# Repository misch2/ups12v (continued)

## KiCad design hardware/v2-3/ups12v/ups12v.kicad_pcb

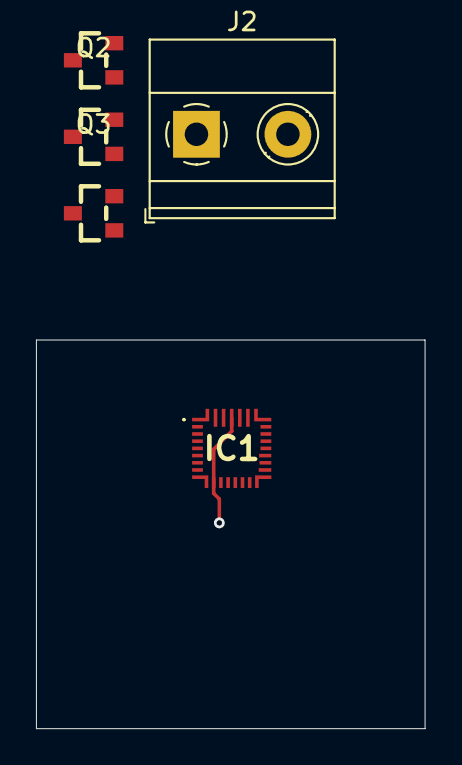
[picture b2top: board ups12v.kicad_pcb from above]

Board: 4 copper layers, 21.6 x 21.6 mm, 5 parts (0 on the bottom side), 10 nets.

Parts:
IC1: BQ25798RQMR
J2: BATTERY (BMS); TerminalBlock_Phoenix_MKDS-1,5-2-5.08_1x02_P5.08mm_Horizont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
Q1, Q2, Q3: SI2312CDS-T1-GE3; SOT-23_L2.9-W1.3-P1.90-LS2.4-BR

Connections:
BAT: IC1.22 (BAT_1), IC1.23 (BAT_2), Q3.2 (S)
GND: IC1.10 (ACDRV2), IC1.13 (~CE), IC1.27 (GND), J2.2
unnamed: Q1.2 (S), Q2.2 (S)
unnamed: Q1.1 (G), Q2.1 (G)
unnamed: J2.1, Q3.3 (D)
SDRV: IC1.24 (SDRV_1), IC1.33 (SDRV_2), Q3.1 (G)
STAT: IC1.1 (STAT_1), IC1.30 (STAT_2)
TS: IC1.16 (TS_1), IC1.32 (TS_2)
VBUS: IC1.2 (VBUS_1), IC1.3 (VBUS_2), IC1.8 (VAC2), Q2.3 (D)
VIN1: IC1.9 (VAC1_1), IC1.31 (VAC1_2), Q1.3 (D)

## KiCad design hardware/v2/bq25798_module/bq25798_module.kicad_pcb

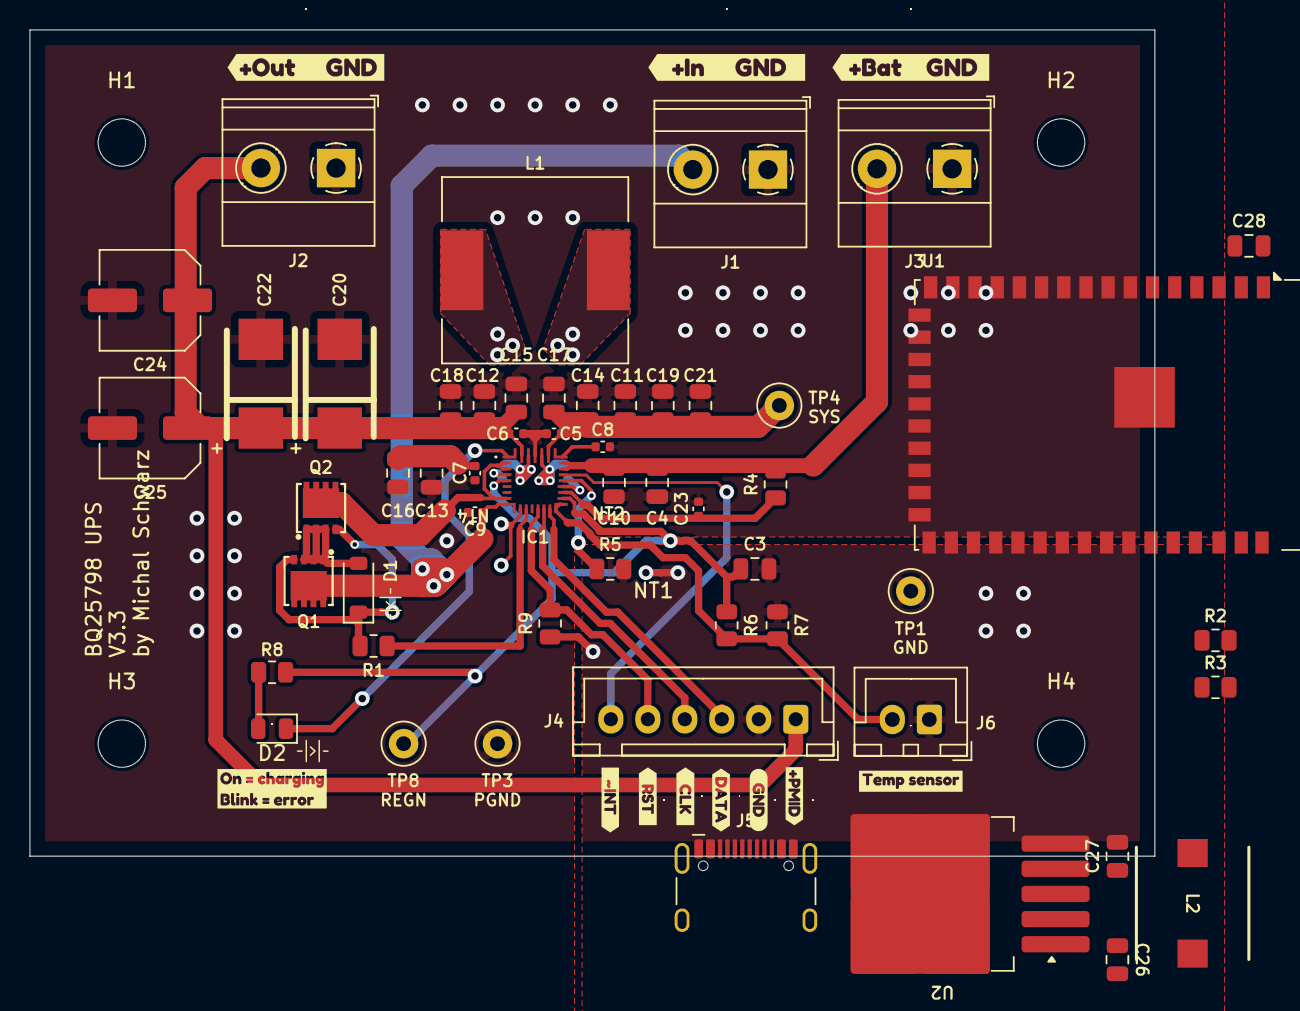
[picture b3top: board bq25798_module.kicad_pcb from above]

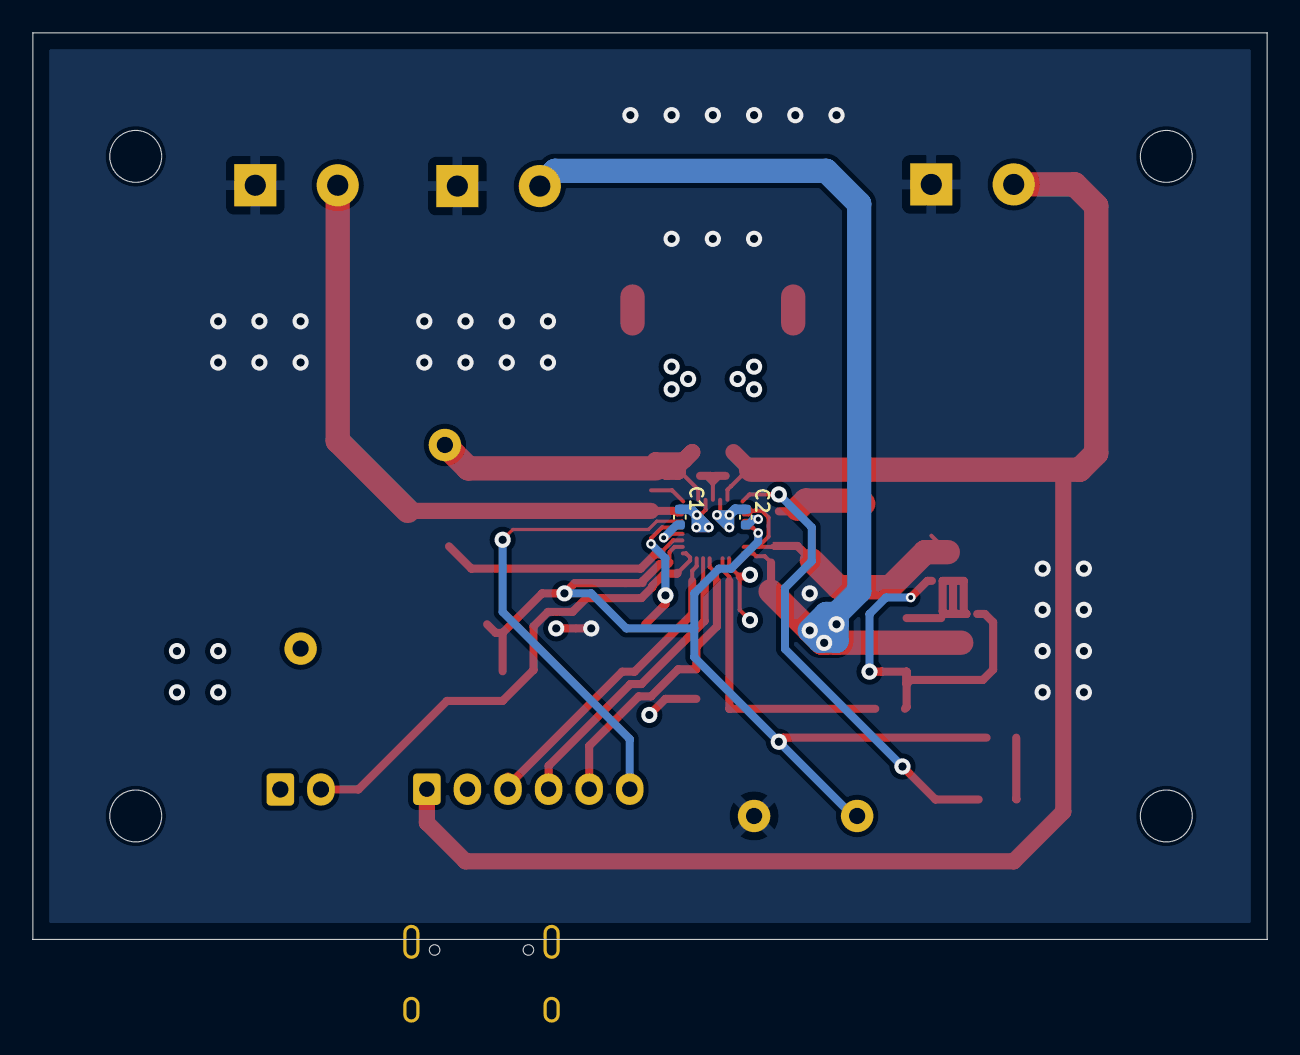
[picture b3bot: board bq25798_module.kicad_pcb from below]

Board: 4 copper layers, 76.0 x 55.9 mm, 74 parts (2 on the bottom side), 35 nets.

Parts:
C1, C2, C23: 47n 25V; C_0402_1005Metric
C3: 4.7u 10V; C_0805_2012Metric
C4, C10, C11, C12, C13, C14, C15, C16, C17, C18, C19, C21, C28: 10u 25V; C_0805_2012Metric
C5, C6, C7, C9: 100n 25V; C_0402_1005Metric
C8: 1nF, 50V; C_0402_1005Metric
C20, C22: 47u POSCAP; CASE-D_7343
C24, C25: 47u low ESR; C_Elec_6.3x5.8
C26: 470u 50V; C_0805_2012Metric
C27: 220u 25V; C_0805_2012Metric
D1: 12V; D_SOD-123
D2: LED; LED_0805_2012Metric
H1, H2, H3, H4: MountingHole; MountingHole_3.2mm_M3
IC1: BQ25798RQMR; BQ25798RQMR_smaller_protected_area
J1: Input 12V DC; TerminalBlock_Phoenix_MKDS-1,5-2-5.08_1x02_P5.08mm_Horizont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
J2: Output 12V DC; TerminalBlock_Phoenix_MKDS-1,5-2-5.08_1x02_P5.08mm_Horizont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
J3: Battery; TerminalBlock_Phoenix_MKDS-1,5-2-5.08_1x02_P5.08mm_Horizont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
J4: Conn_01x06_Pin; JST_XH_B6B-XH-A_1x06_P2.50mm_Vertical
J5: USB_C_Receptacle_USB2.0_14P; USB_C_Receptacle_HCTL_HC-TYPE-C-16P-01A
J6: NTC temp sensor; JST_XH_B2B-XH-A_1x02_P2.50mm_Vertical
L1: 2.2uH; L_12x12mm_H6mm
L2: 68 uH; INDPM7676X435N
NT1, NT2, NT4: NetTie-2_SMD_Pad0.5mm
Q1, Q2: AON7528; DFN-8_L3.3-W3.3-P0.65-BL-3
R1: 270R; R_0805_2012Metric
R2, R3: 5k1; R_0805_2012Metric
R4: 100R; R_0805_2012Metric
R5: 27k 1-2%; R_0805_2012Metric
R6: 5k6; R_0805_2012Metric
R7: 33k; R_0805_2012Metric
R8: 2k2; R_0805_2012Metric
R9: 10k; R_0805_2012Metric
TP1: GND; TestPoint_Loop_D1.80mm_Drill1.0mm_Beaded
TP3: PGND; TestPoint_Loop_D1.80mm_Drill1.0mm_Beaded
TP4: SYS; TestPoint_Loop_D1.80mm_Drill1.0mm_Beaded
TP8: REGN; TestPoint_Loop_D1.80mm_Drill1.0mm_Beaded
U1: ESP32-S2-WROVER
U2: LM2596S-3.3; TO-263-5_TabPin3
kibuzzard-680F50CE: G***; kibuzzard-680F50CE
kibuzzard-680F50E1: G***; kibuzzard-680F50E1
kibuzzard-680F50F5: G***; kibuzzard-680F50F5
kibuzzard-680F5553: G***; kibuzzard-680F5553
kibuzzard-680FCC32: G***; kibuzzard-680FCC32
kibuzzard-6810EFE9: G***; kibuzzard-6810EFE9
kibuzzard-6810F0BF: G***; kibuzzard-6810F0BF
kibuzzard-6810F0CD: G***; kibuzzard-6810F0CD
kibuzzard-6810F0D5: G***; kibuzzard-6810F0D5
kibuzzard-6810F062: G***; kibuzzard-6810F062
kibuzzard-68570239: G***; kibuzzard-68570239

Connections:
/I2C_SCL: IC1.14 (SCL), J4.4
/I2C_SDA: IC1.15 (SDA), J4.3
/~INT: IC1.21 (~INT), J4.6
/~RST: IC1.13 (~CE), J4.5, R9.2
BATTERY: C4.1, C10.1, IC1.22 (BAT_1), IC1.23 (BAT_2), J3.2, R4.2
BTST1: C2.1, IC1.4 (BTST1)
BTST2: C1.2, IC1.19 (BTST2)
GND: C3.2, C26.2, C27.2, C28.2, IC1.10 (ACDRV2), J4.2, J5.A1 (GND), J5.A12 (GND), J5.B1 (GND), J5.B12 (GND), J5.S1 (SHIELD), J6.1, NT1.1, R2.1, R3.1, R5.2, R7.1, R9.1, TP1.1, U1.1 (GND), U1.26 (GND), U1.42 (GND), U1.43 (GND), U2.3 (GND), U2.5 (~ON/OFF)
ILIM_HIZ: IC1.17 (ILIM_HIZ), NT2.1
unnamed: D1.2 (A), Q1.1 (S), Q1.2 (S), Q1.3 (S), Q2.1 (S), Q2.2 (S), Q2.3 (S)
unnamed: D1.1 (K), Q1.4 (G), Q2.4 (G), R1.2
unnamed: D2.2 (A), R8.2
unnamed: IC1.11 (ACDRV1), R1.1
unnamed: C23.1, IC1.18 (BATP), R4.1
unnamed: IC1.20 (PROG), R5.1
unnamed: IC1.2 (VBUS_1), IC1.3 (VBUS_2), IC1.8 (VAC2), NT4.1
unnamed: J5.A5 (CC1), R2.2
unnamed: J5.B5 (CC2), R3.2
unnamed: NT4.2, Q2.5 (D), Q2.6 (D), Q2.7 (D), Q2.8 (D), Q2.9 (D)
unnamed: C27.1, C28.1, L2.1, U1.2 (3V3), U2.4 (FB)
unnamed: J5.A6 (D+), J5.B6 (D+), U1.23 (USB_D+)
unnamed: J5.A7 (D-), J5.B7 (D-), U1.22 (USB_D-)
unnamed: L2.2, U2.2 (OUT)
unnamed: C26.1, J5.A4 (VBUS), J5.A9 (VBUS), J5.B4 (VBUS), J5.B9 (VBUS), U2.1 (VIN)
PGND: C4.2, C5.2, C6.2, C7.2, C8.2, C9.2, C10.2, C11.2, C12.2, C13.2, C14.2, C15.2, C16.2, C17.2, C18.2, C19.2, C20.2, C21.2, C22.2, C23.2, C24.2, C25.2, IC1.27 (GND), J1.1, J2.1, J3.1, NT1.2, TP3.1
PMID: C6.1, C12.1, C15.1, C18.1, C20.1, C22.1, C24.1, C25.1, IC1.29 (PMID), J2.2, J4.1
REGN: C3.1, IC1.5 (REGN), NT2.2, R6.1, R8.1, TP8.1
SDRV: C8.1, IC1.24 (SDRV_1), IC1.33 (SDRV_2)
STAT: D2.1 (K), IC1.1 (STAT_1), IC1.30 (STAT_2)
SW1: C2.2, IC1.28 (SW1), L1.2
SW2: C1.1, IC1.26 (SW2), L1.1
SYS: C5.1, C11.1, C14.1, C17.1, C19.1, C21.1, IC1.25 (SYS), TP4.1
TS: IC1.16 (TS_1), IC1.32 (TS_2), J6.2, R6.2, R7.2
VBUS: C7.1, C13.1, C16.1
VIN1: C9.1, IC1.9 (VAC1_1), IC1.31 (VAC1_2), J1.2, Q1.5 (D), Q1.6 (D), Q1.7 (D), Q1.8 (D), Q1.9 (D)

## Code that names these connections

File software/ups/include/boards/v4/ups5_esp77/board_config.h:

#pragma once

#include "secret/michal_config.h"

#define BOARD_NAME "esp77"
#define DEVICE_NAME "bq25798-ups5"
#define HOSTNAME BOARD_NAME "-" DEVICE_NAME

// U1 GPIO4 = MCU_SDA, GPIO5 = MCU_SCL. MCU_STATUS_LED is an unconnected GPIO3 net.
constexpr Config::Pins boardPins{4, 5, -1, true, 0};  // GPIO0 = MCU_CHG_ARM, active HIGH.

// Start with default config and override specific values
Config config = []() {
  Config cfg = michal_config;
  cfg.pins = boardPins;

  cfg.hardwareVersion = Config::HardwareVersion::V4_0;

  cfg.battery.name = "Liitokala";
  cfg.battery.capacity_mAh = 3400;
  cfg.battery.maxChargeCurrent_mA = 700;          // Standard 0.25C charge current for 3400 mAh cells (fast is 0.5C, i.e., 1700 mA)
  cfg.battery.approx80PercentCapacity_mV = 3920;  // Replace with the verified voltage for your cells. Zero is rejected.

  cfg.network.syslog.myHostname = BOARD_NAME;
  cfg.network.syslog.myAppname = DEVICE_NAME;
  cfg.network.mqtt.haDeviceName = HOSTNAME;

  cfg.power.backupMode = Config::Power::BackupMode::VSYS_UNINTERRUPTED;

  cfg.power.input.retryUnqualifiedAdapter = true;  // Enable retry for USB-PD trigger which changes the input detection state

  cfg.power.charger.chargeProfile.mode = ChargeControl::Mode::APPROX_80;
  cfg.power.charger.ICHG_mA = 500;

  return cfg;
}();

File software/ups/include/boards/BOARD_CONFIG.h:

// Example file

#define I2C_SDA_PIN 21
#define I2C_SCL_PIN 22
#define LED_PIN 2  // GPIO pin for the LED

#define HOSTNAME "ups1"

constexpr SyslogConfig syslogConfig{.serverHostname = "logs.lan", .serverPort = 514, .myHostname = HOSTNAME, .myAppname = "bq25798"};

#define MQTT_SERVER "mqtt.lan"
#define MQTT_PORT 1883
#define MQTT_USER "mqtt_user"
#define MQTT_PASSWORD "secret_password"
#define MQTT_HA_DEVICENAME HOSTNAME

#define VINDPM_mV 12000  // Input voltage DPM threshold in mV
#define IINDPM_mA 3000   // Input current DPM threshold in mA

#define VOTG_mV 12000  // Output voltage for OTG mode
#define IOTG_mA 3200   // Output current for OTG mode in mA

#define BATTERY_CELL_COUNT 4                 // Number of battery cells in series
#define VBAT_CHG_ENABLE_BELOW_CELL_mV 4150   // Lower voltage at which the charger is enabled in mV
#define VBAT_CHG_DISABLE_ABOVE_CELL_mV 4155  // Higher Voltage at which the charger is disabled in mV
#define ICHG_mA 500                          // Charge current in mA (max)

// Battery temperature reporting + resistor divider network for the NTC sensor:
constexpr TemperatureSensorConfig temperatureSensorConfig{.R_vregn = 5600, .R_gnd = 33000, .resistance_25degC = 10000.0, .beta = 3435.0};

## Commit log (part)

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2024-03-01 esphome
2024-05-16 docs: features
2024-11-19 test
2024-11-20 bascic library methods
2024-11-20 test improvements
2025-04-19 update interactive BOM
2025-04-19 detect communication success
2025-04-24 add test program
2025-04-26 track changes
2025-04-29 v2.1 final
2025-04-30 update test program for esp32
2025-04-30 docs for v2
2025-04-30 chore: fix versions, add PDF schematics
2025-04-30 chore: update folder structure
2025-05-07 wip add project to show changes
2025-05-26 add thermal reliefs, simplify PCB
2025-06-01 add power output to the J4
2025-06-02 update board for powering the controller, add controller board
2025-06-21 temporary changes to PCB and schematics
2025-06-22 wip ESP32 schematics
2025-06-22 update documentation
2025-06-22 Fix invalid connections
2025-06-22 v3.3b
2025-06-22 update controller board too
2025-06-30 sw v1
2025-06-30 fix syslog
2025-06-30 more robust sw
2025-06-30 MQTT data
2025-07-01 fix MQTT discovery topics
2025-07-01 simplification
2025-07-01 add calculated values
2025-07-01 works in HA and Grafana
2025-07-01 clean up the code
2025-07-02 fix charger check
2025-07-02 move MQTT/HA code to a separate class
2025-07-02 move LED blinking to a separate class
2025-07-02 tmp investigation
2025-07-02 fix log to serial
2025-07-02 fully working version
2025-07-02 use binary sensor for some ENUMs too
2025-07-02 fix publishing the config topics
2025-07-02 fix charger enable/disable, cleanup
2025-07-02 tidy up the code
2025-07-02 update values on larger change too
2025-07-03 further simplification
2025-07-04 remove unnecessary file
2025-07-04 example config file to satisfy IDE and syntax checkec
2025-07-04 fix the constants
2025-07-04 reset button
2025-07-05 better config
2025-07-05 refactor, improve MQTT reconnection and OTA
2025-07-06 cleaner configuration
2025-07-06 tidy up
2025-07-10 fix missing configuration
2025-07-10 more logging, add checks for cell count
2025-07-12 autodetect cell count by RPROG
2025-07-12 publish battery cell count via mqtt
2025-07-12 update icon
2025-08-10 fix unnecessary logging
2025-11-13 fix backup recovery timer issue
2025-11-17 feat: log reset reason for better debugging
2025-11-17 fix: prevent inability to switch back to online power
2025-11-17 fix: enable battery discharge current sensing
2025-11-17 chore: update version
2025-11-19 chore: configurable AC waiting period
2025-11-19 chore: configurable HW version
2025-11-25 feat: configurable VBUS switchover percentage
2025-11-25 fix: minimum cell voltage
2025-11-27 feat: add an online VSYS_BACKUP_MODE
2025-11-29 chore: refactor config
2025-11-29 refactor: better structured config
2025-11-29 refactor: further config improvements
2025-11-30 refactor: remove default_config, simplify
2025-12-09 feat: proper device model reporting
2025-12-09 fix device model info
